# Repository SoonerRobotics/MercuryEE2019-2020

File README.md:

# Mercury EE 2019-2020
## Electrical Team Projects
Our stuff needs to **_git gud_**

## PCBs

### Arduino Breakout Board
Interfaces with an Arduino Nano, IMU, motor controller, and encoders.

### Sensor Board 
Interfaces with an Arduino Nano, IMU, and multiple ultrasonic sensors. 
 
### Power Module
Acts as a motherboard for a buck converter module.

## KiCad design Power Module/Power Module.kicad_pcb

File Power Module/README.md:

# Arduino Breakout Board (Control)

Designed to output a lower voltage than given.

* Convert 12V to 5V via the buck converter 
* 3A fuse 

## Block Diagram

Insert eventually

## Peripherals

### Fuse 

* [Fuse]()

### Buck COnverter

* [LM2956](http://tpelectronic.ir/datasheets/20150123144301750.pdf)

## Images

## Designers

* **Olivia Wolfe** - *PCB design*

## Built With

* [KiCad](https://kicad-pcb.org/) - The PCB design software used

## Errata

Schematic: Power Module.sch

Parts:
F1, F2, F3: 3A Fuse; 646-SERIESHOLDER
J1, J2, J6: Screw_Terminal_01x02; TerminalBlock_MetzConnect_Type094_RT03502HBLU_1x02_P5.00mm_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
J3, J4, J5: Conn_01x02; JST_EH_B2B-EH-A_1x02_P2.50mm_Vertical
U1, U2, U3: LM2596

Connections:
+12V: F1.2, F2.2, F3.2, J1.2, J2.2, J6.2
GND: J1.1, J2.1, J3.2, J4.2, J5.2, J6.1, U1.1 (IN-), U1.3 (OUT-), U2.1 (IN-), U2.3 (OUT-), U3.1 (IN-), U3.3 (OUT-)
unnamed: F1.1, U1.2 (IN+)
unnamed: F2.1, U2.2 (IN+)
unnamed: F3.1, U3.2 (IN+)
unnamed: J3.1, U1.4 (OUT+)
unnamed: J4.1, U2.4 (OUT+)
unnamed: J5.1, U3.4 (OUT+)

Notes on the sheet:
3 Buck converters, in v2 all the power modules are going on the same board. This means we will need wide traces in the PCB.
3 Screw terminals, 1 screw terminal will be for the 12V Battery in and the other 2 will be for 12V out. One 12V out will power the motor controller, and the other will be for anything else

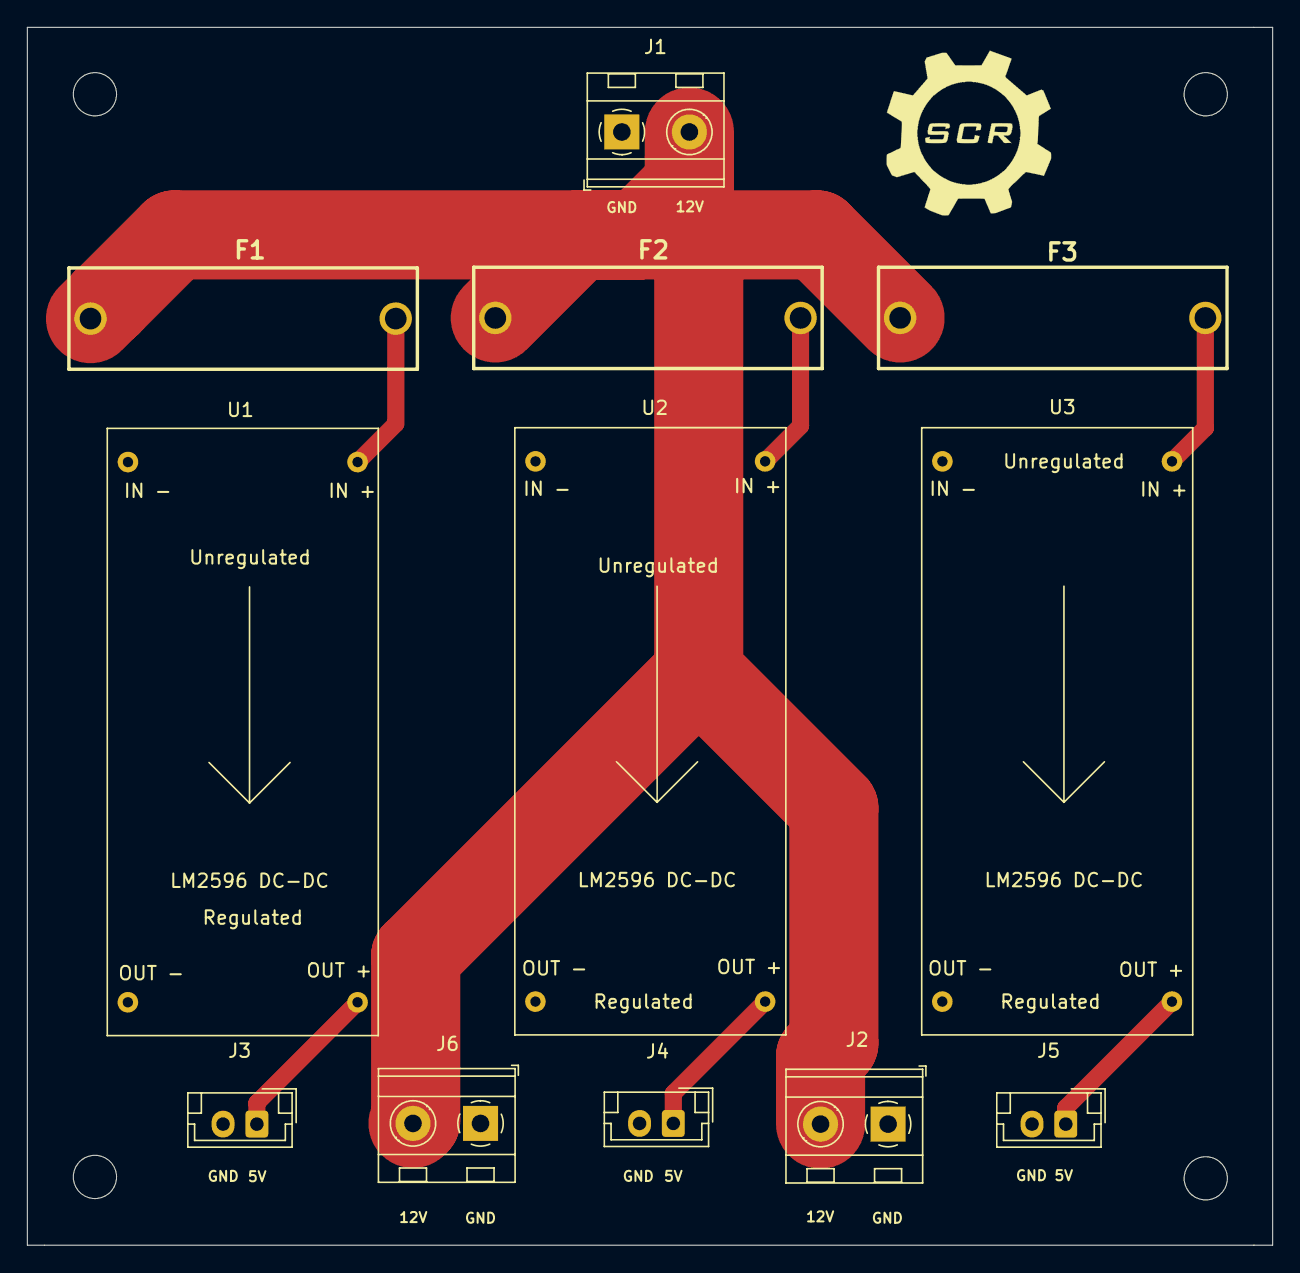
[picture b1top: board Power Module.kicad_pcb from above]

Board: 2 copper layers, 92.2 x 90.2 mm, 12 parts (0 on the bottom side), 8 nets.

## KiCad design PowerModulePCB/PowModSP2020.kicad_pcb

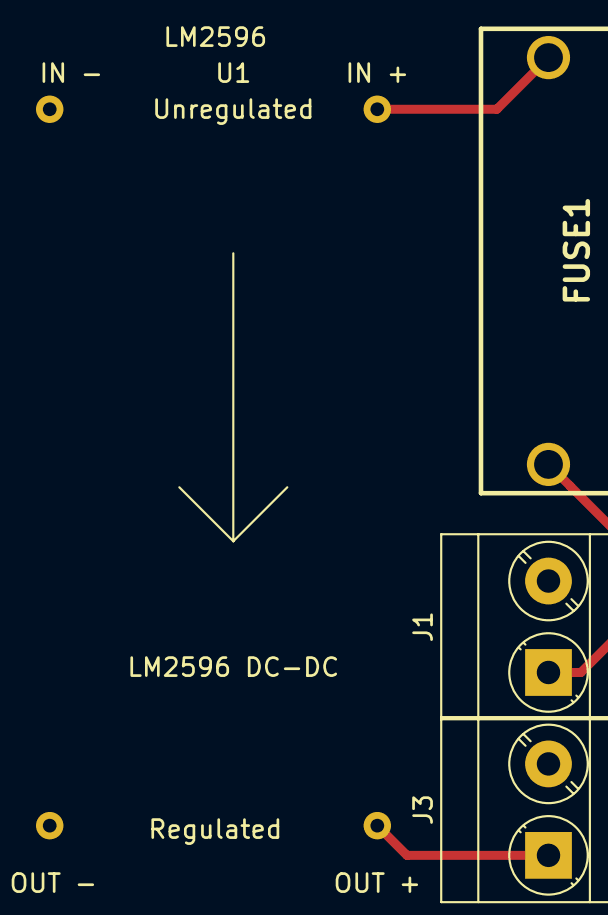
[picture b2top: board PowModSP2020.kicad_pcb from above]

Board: 2 copper layers, 4 parts (0 on the bottom side), 4 nets.

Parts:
FUSE1: 64600001003; 646-SERIESHOLDER
J1, J3: Screw_Terminal_01x02; TerminalBlock_Phoenix_MKDS-3-2-5.08_1x02_P5.08mm_Horizontal
U1: LM2596

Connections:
GND: J1.2, J3.2, U1.1, U1.3
unnamed: FUSE1.1, U1.2
unnamed: FUSE1.2, J1.1
unnamed: J3.1, U1.4

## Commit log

2019-06-27 Add files via upload
    Datasheet for L298N chip. Dual H-Bridge Motor Controller.
2020-01-27 Added ground fill, fixed edge cuts, fixed 90 degree angles,
2020-01-29 fixed more 90 degree angles, Added drill holes
2020-01-29 Fixed library on the power module? Deleted hanging node on Schematic
2020-01-29 Possible library fix
2020-01-31 Testing access to git
2020-01-31 Folder for KiCad Refrences
2020-01-31 this is a test please work
2020-01-31 This is another test
2020-01-31 Initial Sensor Board Push
2020-01-31 Create Data Sheets
2020-01-31 Added DataSheets folder
2020-02-04 Completly rerouted traces across the board, added more space between the traces, added more description for the pads
2020-02-04 made the traces on arduino to buffer pins thinner, gave more space in between the traces, and added more data sheets to git
2020-02-05 updated sensor board worked on by olivia ??? changes made
2020-02-07 Add links for part search
2020-02-07 switched pins on ultrasonic to PWM pins and switched some wiring
2020-02-07 switched pins on the ultrasonic and made traces larger in the sensor board
2020-02-07 File management
2020-02-07 Adjusted the board designed by the team
    Adjusted the track width for the 5 volts
    Added text on silk screen for each connection
    added mounting holes
2020-02-11 Create EEResources
2020-02-11 Rename EEResources to EEResources.md
2020-02-12 Added gerber files for SensorBoard and ArduinoBreakoutboard
2020-02-20 added colored Schematics into PDF folder
2020-02-20 Added colored PDF and added a Library file in the project
2020-02-20 Added colored schematic
2020-02-20 Changed DataSheets to datasheets
2020-02-21 Reorganize files
2020-02-21 Update READMEs
2020-02-21 Move files around
2020-02-21 Add datasheets folder back
2020-02-21 Add git ignore file
2020-02-21 Update gitignore
2020-02-21 Added updated schematic for breakoutboard
2020-03-03 added an updated schematic with cleanner wire routing and updated the pcb for the schematic
2020-03-05 Started work on v2 of Power Module
    Updated and made schematic for v2 of power Module
    Reworked PCB to address the new schematic
2020-03-05 started work on v2 of the Breakout board
    Added Schematic for v2 of the Board
    Updated PCB to address the changes done to the Schematic
2020-03-06 Finished PCB redesign needs review
2020-03-06 added 2 more connectors for servos to the schematic and PCB
    Updated and finished the PCB for V2
2020-03-06 Added silkscreen indicators for the servo motor JST
    Added additional mounting holes
2020-03-09 Changed pins of the servo to PWM pins
    deleted unneccesary schematic files
2020-03-09 deleted unnecesary PDFs and added Gerber files for v2
